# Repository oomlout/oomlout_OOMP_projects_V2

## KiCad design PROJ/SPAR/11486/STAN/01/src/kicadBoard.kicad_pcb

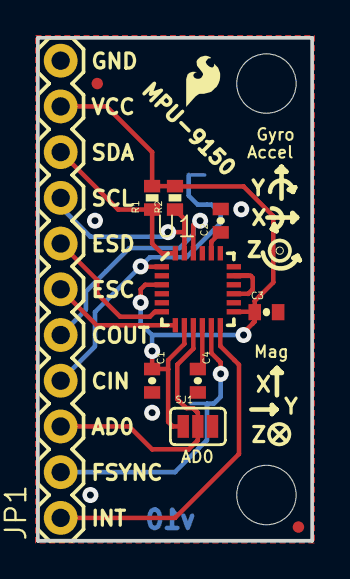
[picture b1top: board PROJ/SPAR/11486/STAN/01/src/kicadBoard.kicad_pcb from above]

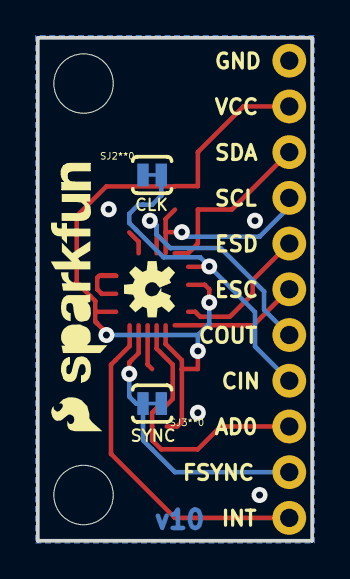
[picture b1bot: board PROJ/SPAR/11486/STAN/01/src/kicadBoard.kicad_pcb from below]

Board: 2 copper layers, 15.2 x 27.9 mm, 19 parts (5 on the bottom side), 13 nets.

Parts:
C1, C4: 0.1uF; 0402-CAP
C2: 2.2nF; 0402-CAP
C3: 10nF; 0402-CAP
JP1: M11PTH; 1X11
JP2, JP3: STAND-OFF
JP4: LOGO-SFENW2; SFE-NEW-WEB
JP5, JP6: LOGO-SFESK; SFE-LOGO-FLAME
JP7, JP8: FIDUCIALUFIDUCIAL; MICRO-FIDUCIAL
R1, R2: 10k; 0402-RES
SJ1: SJ_3_PASTE2&3
SJ2**0, SJ3**0: SOLDERJUMPERTRACE; SJ_2S-TRACE
U1: MPU-9150; QFN-24-NP
U$1: OSHW-LOGOS; OSHW-LOGO-S

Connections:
AD0: JP1.3, SJ1.2, U1.9
CLKIN: JP1.4, SJ2**0.2, U1.1
CLKOUT: JP1.5, U1.22
ESC: JP1.6, U1.7
ESD: JP1.7, U1.6
FSYNC: JP1.2, SJ3**0.2, U1.11
GND: C1.2, C2.2, C3.2, C4.2, JP1.11, SJ1.3, SJ2**0.1, SJ3**0.1, U1.15, U1.17, U1.18
INT: JP1.1, U1.12
unnamed: C2.1, U1.20
unnamed: C4.1, U1.10
SCL: JP1.8, R2.1, U1.23
SDA: JP1.9, R1.1, U1.24
VCC: C1.1, C3.1, JP1.10, R1.2, R2.2, SJ1.1, U1.3, U1.8, U1.13

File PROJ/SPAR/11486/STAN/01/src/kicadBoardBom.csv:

"Id";"Designator";"Package";"Quantity";"Designation";"Supplier and ref";
1;"JP5,JP6";"SFE-LOGO-FLAME";2;"LOGO-SFESK";;;
2;"U1";"QFN-24-NP";1;"MPU-9150";;;
3;"C1,C4";"0402-CAP";2;"0.1uF";;;
4;"JP8,JP7";"MICRO-FIDUCIAL";2;"FIDUCIALUFIDUCIAL";;;
5;"R2,R1";"0402-RES";2;"10k";;;
6;"SJ1";"SJ_3_PASTE2&3";1;"";;;
7;"C2";"0402-CAP";1;"2.2nF";;;
8;"JP1";"1X11";1;"M11PTH";;;
9;"JP2,JP3";"STAND-OFF";2;"STAND-OFF";;;
10;"C3";"0402-CAP";1;"10nF";;;
11;"SJ2**0,SJ3**0";"SJ_2S-TRACE";2;"SOLDERJUMPERTRACE";;;
12;"U$1";"OSHW-LOGO-S";1;"OSHW-LOGOS";;;
13;"JP4";"SFE-NEW-WEB";1;"LOGO-SFENW2";;;

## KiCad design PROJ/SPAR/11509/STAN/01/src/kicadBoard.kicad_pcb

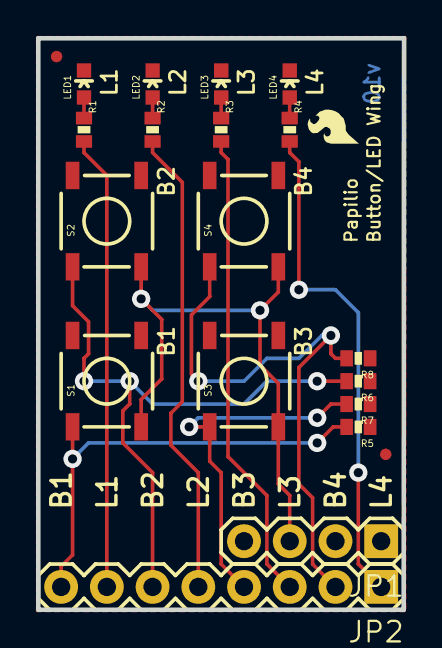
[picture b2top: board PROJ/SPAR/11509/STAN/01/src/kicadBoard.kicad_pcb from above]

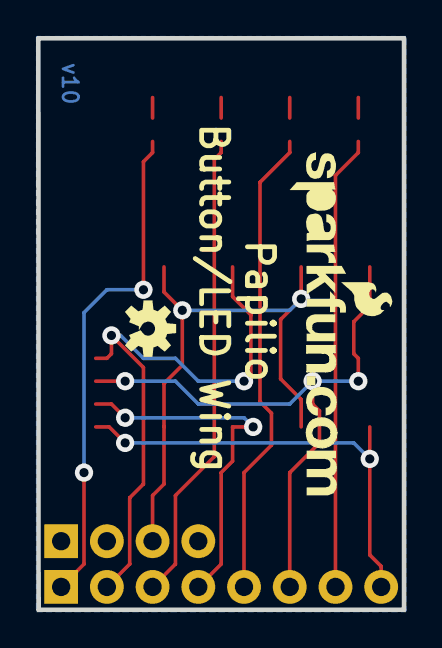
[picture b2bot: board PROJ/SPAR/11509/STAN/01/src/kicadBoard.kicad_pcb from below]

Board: 2 copper layers, 20.3 x 31.8 mm, 24 parts (2 on the bottom side), 14 nets.

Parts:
FRAME1: FRAME-LETTER; CREATIVE_COMMONS
JP1: 1X04
JP2: 1X08
JP3: LOGO-SFESK; SFE-LOGO-FLAME
JP4: LOGO-SFENEW; SFE-NEW-WEBLOGO
JP5, JP6: FIDUCIALUFIDUCIAL; MICRO-FIDUCIAL
LED1: Red; LED-0603
LED2: Yellow; LED-0603
LED3: Green; LED-0603
LED4: Blue; LED-0603
R1, R2, R3, R4: 220; 0402-RES
R5, R6, R7, R8: 10k; 0402-RES
S1: Button 1; TACTILE_SWITCH_SMD
S2: Button 2; TACTILE_SWITCH_SMD
S3: Button 3; TACTILE_SWITCH_SMD
S4: Button 4; TACTILE_SWITCH_SMD
U$1: OSHW-LOGOS; OSHW-LOGO-S

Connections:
3.3V: JP1.3, S1.3, S2.3, S3.3, S4.3
GND: JP1.1, LED1.C, LED2.C, LED3.C, LED4.C, R5.1, R6.1, R7.1, R8.1
LED1: JP2.7, R1.2
LED2: JP2.5, R2.2
LED3: JP2.3, R3.2
LED4: JP2.1, R4.2
unnamed: LED1.A, R1.1
unnamed: LED3.A, R3.1
unnamed: LED2.A, R2.1
unnamed: LED4.A, R4.1
PB1: JP2.8, R5.2, S1.1
PB2: JP2.6, R6.2, S2.1
PB3: JP2.4, R7.2, S3.1
PB4: JP2.2, R8.2, S4.1

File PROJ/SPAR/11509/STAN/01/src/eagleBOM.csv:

"Part";"Value";"Device";"Package";"Description";"";
"FRAME1";"FRAME-LETTER";"FRAME-LETTER";"CREATIVE_COMMONS";"Schematic Frame";"";
"JP1";"";"M04PTH";"1X04";"Header 4";"";
"JP2";"";"M081X08";"1X08";"Header 8";"";
"JP3";"LOGO-SFESK";"LOGO-SFESK";"SFE-LOGO-FLAME";"Spark Fun Electronics PCB Logo";"";
"JP4";"LOGO-SFENEW";"LOGO-SFENEW";"SFE-NEW-WEBLOGO";"Spark Fun Electronics PCB Logo";"";
"JP5";"FIDUCIALUFIDUCIAL";"FIDUCIALUFIDUCIAL";"MICRO-FIDUCIAL";"Fiducial Alignment Points";"";
"JP6";"FIDUCIALUFIDUCIAL";"FIDUCIALUFIDUCIAL";"MICRO-FIDUCIAL";"Fiducial Alignment Points";"";
"LED1";"Red";"LED0603";"LED-0603";"LEDs";"";
"LED2";"Yellow";"LED0603";"LED-0603";"LEDs";"";
"LED3";"Green";"LED0603";"LED-0603";"LEDs";"";
"LED4";"Blue";"LED0603";"LED-0603";"LEDs";"";
"R1";"220";"RESISTOR0402-RES";"0402-RES";"Resistor";"";
"R2";"220";"RESISTOR0402-RES";"0402-RES";"Resistor";"";
"R3";"220";"RESISTOR0402-RES";"0402-RES";"Resistor";"";
"R4";"220";"RESISTOR0402-RES";"0402-RES";"Resistor";"";
"R5";"10k";"RESISTOR0402-RES";"0402-RES";"Resistor";"";
"R6";"10k";"RESISTOR0402-RES";"0402-RES";"Resistor";"";
"R7";"10k";"RESISTOR0402-RES";"0402-RES";"Resistor";"";
"R8";"10k";"RESISTOR0402-RES";"0402-RES";"Resistor";"";
"S1";"Button 1";"SWITCH-MOMENTARY-2SMD";"TACTILE_SWITCH_SMD";"Various NO switches- pushbuttons, reed, etc";"";
"S2";"Button 2";"SWITCH-MOMENTARY-2SMD";"TACTILE_SWITCH_SMD";"Various NO switches- pushbuttons, reed, etc";"";
"S3";"Button 3";"SWITCH-MOMENTARY-2SMD";"TACTILE_SWITCH_SMD";"Various NO switches- pushbuttons, reed, etc";"";
"S4";"Button 4";"SWITCH-MOMENTARY-2SMD";"TACTILE_SWITCH_SMD";"Various NO switches- pushbuttons, reed, etc";"";
"U$1";"OSHW-LOGOS";"OSHW-LOGOS";"OSHW-LOGO-S";"Open Source Hardware Logo This logo indicates the piece of hardware it is found on incorporates a OSHW license and/or adheres to the definition of open source hardware found here: http://freedomdefined.org/OSHW";"";

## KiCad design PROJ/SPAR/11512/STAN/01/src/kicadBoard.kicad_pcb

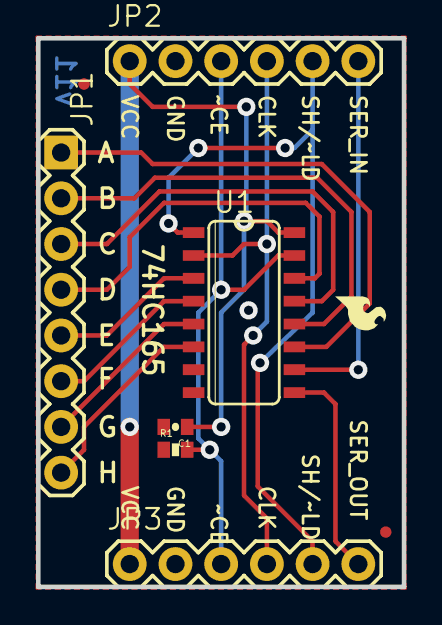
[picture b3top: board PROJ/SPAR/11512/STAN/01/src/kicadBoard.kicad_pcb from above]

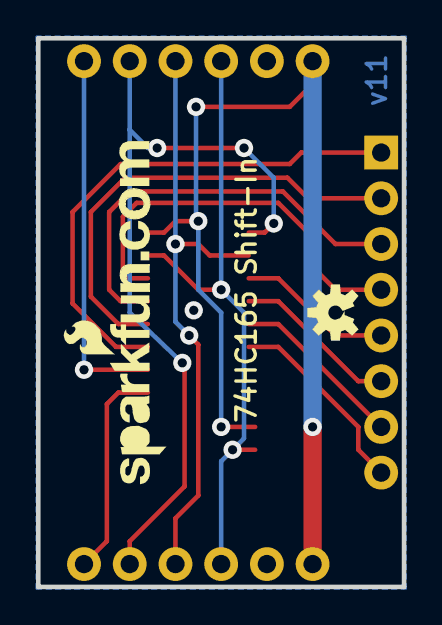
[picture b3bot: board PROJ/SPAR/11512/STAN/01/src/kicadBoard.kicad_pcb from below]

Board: 2 copper layers, 20.3 x 30.5 mm, 12 parts (2 on the bottom side), 15 nets.

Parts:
C1: .1uF; 0402-CAP
FRAME1: FRAME-LETTER; CREATIVE_COMMONS
JP1: 1X08
JP2, JP3: 1X06
JP4: LOGO-SFESK; SFE-LOGO-FLAME
JP5: LOGO-SFENEW; SFE-NEW-WEBLOGO
JP6, JP7: FIDUCIALUFIDUCIAL; MICRO-FIDUCIAL
R1: 10k; 0402-RES
U1: 74HC165D; SO16
U$1: OSHW-LOGOS; OSHW-LOGO-S

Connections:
A: JP1.1, U1.11
B: JP1.2, U1.12
C: JP1.3, U1.13
CLK: JP2.4, JP3.4, U1.2
D: JP1.4, U1.14
E: JP1.5, U1.3
F: JP1.6, U1.4
G: JP1.7, U1.5
GND: C1.2, JP2.2, JP3.2, R1.1, U1.8
H: JP1.8, U1.6
SERIAL_IN: JP2.6, U1.10
SERIAL_OUT: JP3.6, U1.9
SHIFT/~LOAD: JP2.5, JP3.5, U1.1
VCC: C1.1, JP2.1, JP3.1, U1.16
~CLK_ENABLE: JP2.3, JP3.3, R1.2, U1.15

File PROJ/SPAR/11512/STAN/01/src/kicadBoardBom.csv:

"Id";"Designator";"Package";"Quantity";"Designation";"Supplier and ref";
1;"R1";"0402-RES";1;"10k";;;
2;"JP2,JP3";"1X06";2;"";;;
3;"FRAME1";"CREATIVE_COMMONS";1;"FRAME-LETTER";;;
4;"JP7,JP6";"MICRO-FIDUCIAL";2;"FIDUCIALUFIDUCIAL";;;
5;"C1";"0402-CAP";1;".1uF";;;
6;"JP1";"1X08";1;"";;;
7;"JP4";"SFE-LOGO-FLAME";1;"LOGO-SFESK";;;
8;"U1";"SO16";1;"74HC165D";;;
9;"JP5";"SFE-NEW-WEBLOGO";1;"LOGO-SFENEW";;;
10;"U$1";"OSHW-LOGO-S";1;"OSHW-LOGOS";;;

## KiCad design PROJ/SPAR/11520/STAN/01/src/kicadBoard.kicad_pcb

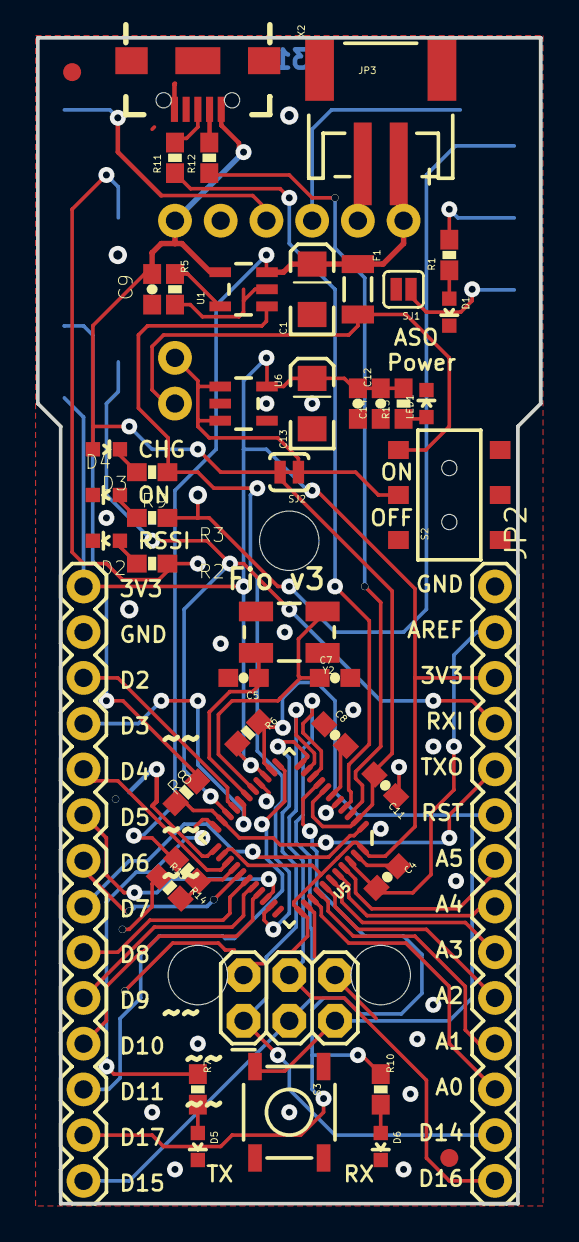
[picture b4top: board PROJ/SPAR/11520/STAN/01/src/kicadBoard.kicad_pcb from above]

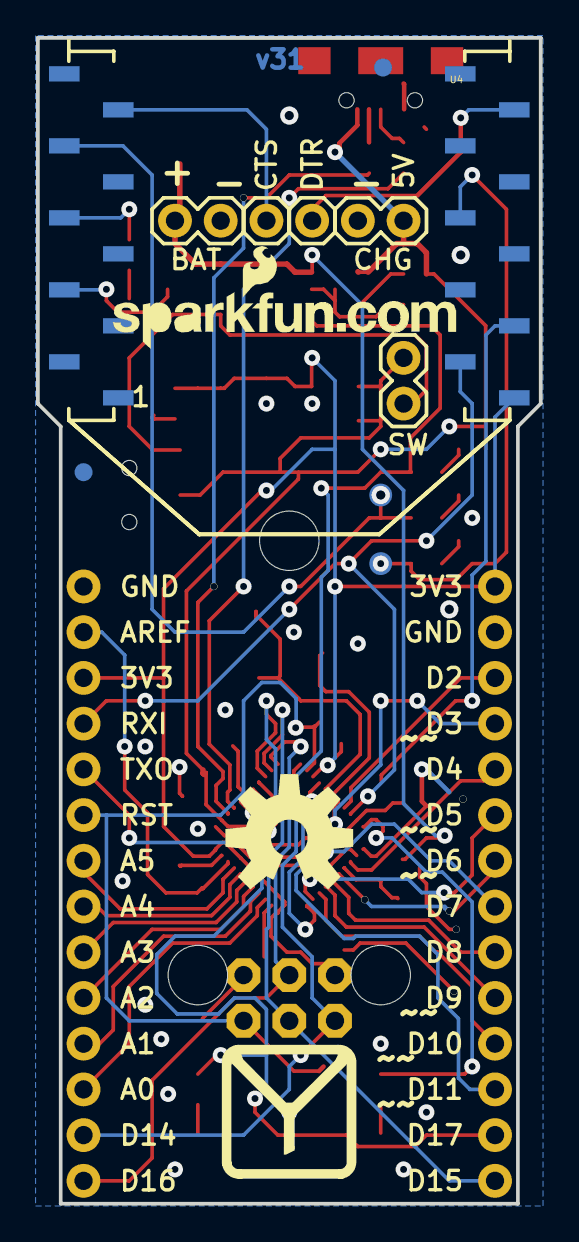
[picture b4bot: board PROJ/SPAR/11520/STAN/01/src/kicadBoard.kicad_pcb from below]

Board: 2 copper layers, 27.9 x 64.8 mm, 66 parts (12 on the bottom side), 55 nets.

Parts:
C1, C13: 10uF; EIA3216
C4, C14: 0.1uF; 0603-CAP
C5, C7: 22pF; 0603-CAP
C8, C11, C12: 1uF; 0603-CAP
C9: 4.7uF; 0603-CAP
D1, D4, D5: Yellow; LED-0603
D2: Green; LED-0603
D3: Red; LED-0603
D6: Blue; LED-0603
F1: PTCSMD; PTC-1206
FRAME1, FRAME2: FRAME-LETTER; CREATIVE_COMMONS
JP1, JP2: M14; 1X14
JP3: JST-2-SMD
JP4: AVR_SPI; 2X3
JP5, JP16, JP17: STAND-OFF
JP6: External Charge; 1X02
JP7: External Switch; 1X02
JP8, JP9: 1X01
JP10, JP11, JP12, JP13: FIDUCIALUFIDUCIAL; FIDUCIAL-1X2
JP14: External Power; 1X02
LED1: Red; LED-0603
LOGO1: OSHW-LOGOL; OSHW-LOGO-L
R1, R2, R3, R7, R10, R13: 330; 0603-RES
R5: 2K; 0603-RES
R6: 10K; 0603-RES
R8: 100; 0603-RES
R9: 470; 0603-RES
R11, R12: 22; 0603-RES
R14, R15: 1k; 0603-RES
S2: Power Switch; AYZ0202
S3: Reset; TACTILE_SWITCH_SMD
SJ1: SOLDERJUMPERNC; SJ_2S
SJ2: USB Power; SJ_2S-TRACE
TP1: RSSI; PAD.03X.05
TP2: ON; PAD.03X.05
U1: MCP73831; SOT23-5
U4: XBEE; XBEE-SMD
U5: ATmega32U4; QFN-44-NOPAD_1_1
U6: MIC5219-3.3; SOT23-5
U$1: LOGO-SFENEW; SFE-NEW-WEBLOGO
U$2: REVISION
U$6: FIO_LOGOV2; FUNNEL_LOGO_BOTTOM_V2
X2: USB_MICROB_PLUGCONN-11752; USB-B-MICRO-SMD_V03
Y2: 8MHz; CRYSTAL-SMD-5X3

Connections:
3.3V: C12.1, C13.A, C14.2, JP1.1, JP2.3, JP4.2, R6.2, R13.2, U4.1, U5.14, U5.24, U5.34, U5.44, U6.5
A0: JP2.12, U5.36
A1: JP2.11, U5.37
A2: JP2.10, U5.38
A3: JP2.9, U5.39
A4: JP2.8, U5.40
A5: JP2.7, U5.41
AREF: C4.2, JP2.2, U5.42
ASSOCIATE: R1.2, U4.15
CHARGE_STAT: R9.1, U1.1, U5.32
CTS: JP8.1, U4.12
D2: JP1.3, U5.19
D3: JP1.4, U5.18
D4: JP1.5, U5.25
D5: JP1.6, U5.31
D6: JP1.7, U5.27
D7: JP1.8, U5.1
D8: JP1.9, U5.28
D9: JP1.10, U5.29
D10: JP1.11, U5.30
D11: JP1.12, U5.12
D17: JP1.13, R10.1, U5.8
D+: R11.1, U5.4
D-: R12.1, U5.3
GND: C1.C, C4.1, C5.2, C7.2, C8.1, C9.2, C11.1, C12.2, C13.C, C14.1, D1.C, D2.C, D3.C, D5.C, D6.C, JP1.2, JP2.1, JP3.1, JP4.6, JP6.1, JP14.1, LED1.C, R5.2, R15.1, S3.1, U1.2, U4.10, U5.5, U5.15, U5.23, U5.33, U5.35, U5.43, U6.2, X2.GND1
MISO: JP2.13, JP4.1, U5.11
MOSI: JP2.14, JP4.4, U5.10
unnamed: R3.2, TP2.P$1, U4.13
unnamed: D1.A, R1.1
unnamed: D2.A, R2.1
unnamed: R2.2, TP1.P$1, U4.6
unnamed: R11.2, X2.D+1
unnamed: D3.A, R3.1
unnamed: R8.2, U4.3
unnamed: D4.C, R9.2
unnamed: F1.2, JP7.2, S2.3
unnamed: R5.1, U1.5
unnamed: SJ1.1, U4.17
unnamed: D5.A, R7.2
unnamed: C7.1, U5.16, Y2.1
unnamed: C5.1, U5.17, Y2.3
unnamed: D6.A, R10.2
unnamed: R12.2, X2.D-1
unnamed: LED1.A, R13.1
RAW: JP7.1, S2.2, SJ2.1, U6.1, U6.3
RST: JP2.6, JP4.5, R6.1, S3.3, U5.13
RXI: JP2.4, U4.2, U5.20
SCK: JP1.14, JP4.3, U5.9
SLEEP_RQ: JP9.1, U4.9
TXLED: R7.1, U5.22
TXO: JP2.5, R8.1, U5.21
UCAP: C8.2, U5.6
USB_VCC: C9.1, C11.2, D4.A, JP6.2, SJ2.2, U1.4, U5.2, U5.7, X2.VBUS
VBATT: C1.A, F1.1, JP3.2, JP14.2, R14.2, U1.3
VBATT_LVL: R14.1, R15.2, U5.26

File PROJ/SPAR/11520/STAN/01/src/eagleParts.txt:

Partlist

Exported from boardEagle.brd at 17/08/2022 21:16

EAGLE Version 9.6.2 Copyright (c) 1988-2020 Autodesk, Inc.

Assembly variant: 

Part     Value                     Package             Library                     Position (inch)       Orientation

C1       10uF                      EIA3216             SparkFun                    (0.55 2)              R90
C4       0.1uF                     0603-CAP            SparkFun-Capacitors         (0.71437008 0.71437008) R225
C5       22pF                      0603-CAP            SparkFun-Capacitors         (0.4 1.15)            R180
C7       22pF                      0603-CAP            SparkFun-Capacitors         (0.6 1.15)            R0
C8       1uF                       0603-CAP            SparkFun-Capacitors         (0.6 1.025)           R315
C9       4.7uF                     0603-CAP            SparkFun-Capacitors         (0.2 2)               R270
C11      1uF                       0603-CAP            SparkFun-Capacitors         (0.71 0.915)          R135
C12      1uF                       0603-CAP            SparkFun-Capacitors         (0.65 1.75)           R270
C13      10uF                      EIA3216             SparkFun                    (0.55 1.75)           R90
C14      0.1uF                     0603-CAP            SparkFun-Capacitors         (0.7 1.75)            R90
D1       Yellow                    LED-0603            SparkFun                    (0.85 1.95)           R180
D2       Green                     LED-0603            SparkFun                    (0.1 1.45)            R90
D3       Red                       LED-0603            SparkFun                    (0.1 1.55)            R90
D4       Yellow                    LED-0603            SparkFun                    (0.1 1.65)            R270
D5       Yellow                    LED-0603            SparkFun                    (0.3 0.125)           R180
D6       Blue                      LED-0603            SparkFun                    (0.7 0.125)           R180
F1       PTCSMD                    PTC-1206            SparkFun                    (0.65 2)              R270
JP1      M14                       1X14                SparkFun                    (0.05 1.35)           R270
JP2      M14                       1X14                SparkFun                    (0.95 1.35)           R270
JP3                                JST-2-SMD           SparkFun                    (0.7 2.42)            R0
JP4      AVR_SPI                   2X3                 SparkFun                    (0.4 0.4)             R0
JP6      External Charge           1X02                SparkFun                    (0.35 2.15)           MR0
JP7      External Switch           1X02                SparkFun                    (0.25 1.85)           MR270
JP8                                1X01                SparkFun                    (0.55 2.15)           MR0
JP9                                1X01                SparkFun                    (0.45 2.15)           MR0
JP10     FIDUCIALUFIDUCIAL         FIDUCIAL-1X2        SparkFun                    (0.85 0.1)            R0
JP11     FIDUCIALUFIDUCIAL         FIDUCIAL-1X2        SparkFun                    (0.025 2.475)         R0
JP12     FIDUCIALUFIDUCIAL         FIDUCIAL-1X2        SparkFun                    (0.295 2.485)         MR0
JP13     FIDUCIALUFIDUCIAL         FIDUCIAL-1X2        SparkFun                    (0.95 1.6)            MR0
JP14     External Power            1X02                SparkFun                    (0.65 2.15)           MR180
LED1     Red                       LED-0603            SparkFun                    (0.8 1.75)            R0
R1       330                       0603-RES            SparkFun-Resistors          (0.85 2.075)          R90
R2       330                       0603-RES            SparkFun-Resistors          (0.2 1.4)             R0
R3       330                       0603-RES            SparkFun-Resistors          (0.2 1.5)             R0
R5       2K                        0603-RES            SparkFun-Resistors          (0.25 2)              R270
R6       10K                       0603-RES            SparkFun-Resistors          (0.41 1.03)           R225
R7       330                       0603-RES            SparkFun-Resistors          (0.3 0.25)            R270
R8       100                       0603-RES            SparkFun-Resistors          (0.275 0.9)           R45
R9       470                       0603-RES            SparkFun-Resistors          (0.2 1.6)             R180
R10      330                       0603-RES            SparkFun-Resistors          (0.7 0.25)            R270
R11      22                        0603-RES            SparkFun-Resistors          (0.25 2.2875)         R90
R12      22                        0603-RES            SparkFun-Resistors          (0.325 2.2875)        R90
R13      330                       0603-RES            SparkFun-Resistors          (0.75 1.75)           R90
R14      1k                        0603-RES            SparkFun-Resistors          (0.2761811 0.72956693) R135
R15      1k                        0603-RES            SparkFun-Resistors          (0.23858268 0.69098425) R315
S2       Power Switch              AYZ0202             SparkFun                    (0.85 1.55)           R90
S3       Reset                     TACTILE_SWITCH_SMD  SparkFun                    (0.5 0.2)             R270
SJ1      SOLDERJUMPERNC            SJ_2S               SparkFun                    (0.75 2)              R180
SJ2      USB Power                 SJ_2S-TRACE         SparkFun                    (0.5 1.6)             R180
TP1      RSSI                      PAD.03X.05          SparkFun                    (0.3 1.4)             MR0
TP2      ON                        PAD.03X.05          SparkFun                    (0.3 1.55)            MR0
U1       MCP73831                  SOT23-5             SparkFun                    (0.4 2)               R90
U4       XBEE                      XBEE-SMD            SparkFun                    (0.5 2.55)            MR180
U5       ATmega32U4                QFN-44-NOPAD_1:1    SparkFun-IC-Microcontroller (0.5 0.8)             R225
U6       MIC5219-3.3               SOT23-5             SparkFun                    (0.4 1.75)            R270
X2       USB_MICROB_PLUGCONN-11752 USB-B-MICRO-SMD_V03 SparkFun-Connectors         (0.3 2.5)             R270
Y2       8MHz                      CRYSTAL-SMD-5X3     SparkFun                    (0.5 1.25)            R180

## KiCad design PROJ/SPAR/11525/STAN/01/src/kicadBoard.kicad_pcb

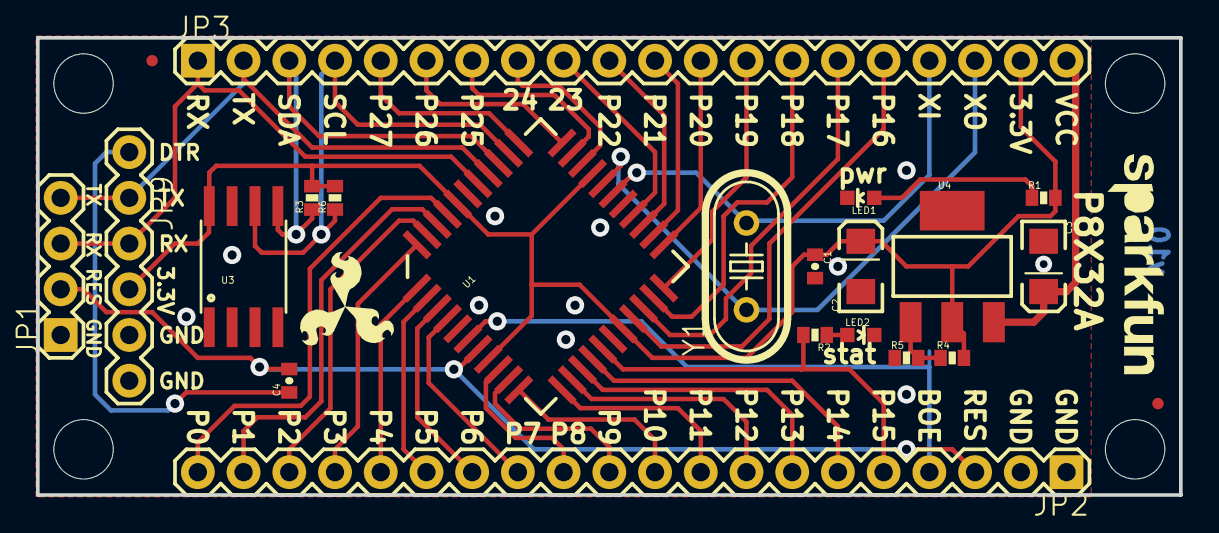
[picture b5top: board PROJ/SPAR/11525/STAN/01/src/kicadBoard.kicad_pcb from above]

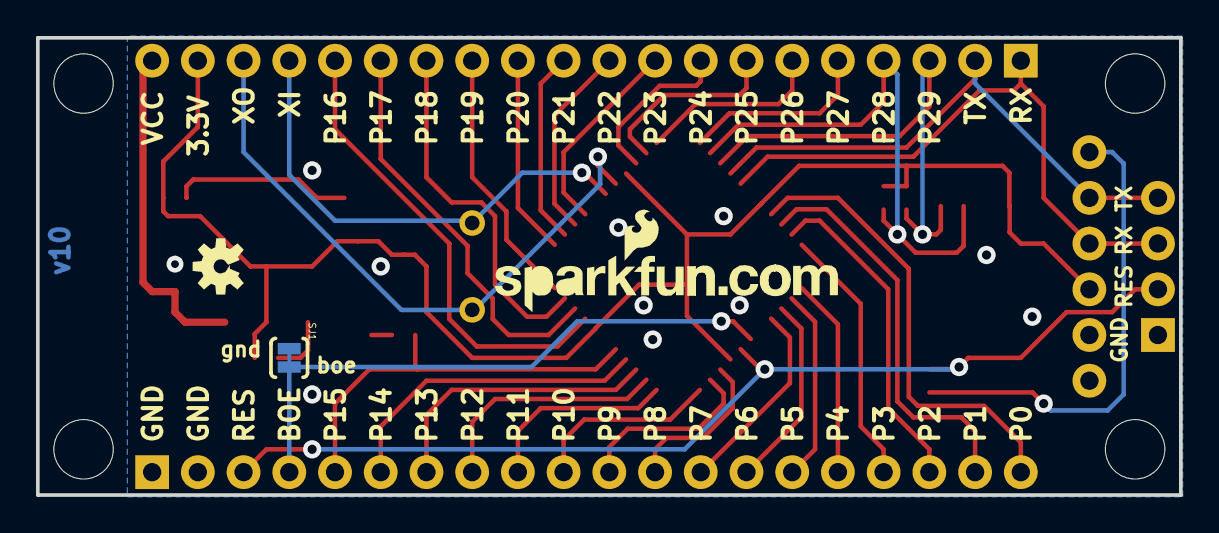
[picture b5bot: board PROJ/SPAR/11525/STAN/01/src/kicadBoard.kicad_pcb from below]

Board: 2 copper layers, 63.5 x 25.4 mm, 34 parts (3 on the bottom side), 43 nets.

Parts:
C1, C4: 0.1uF; 0402-CAP
C2, C3: 10uF; EIA3216
FRAME1: FRAME-LETTER; CREATIVE_COMMONS
JP1: PropPlug; 1X04
JP2, JP3: M20; 1X20
JP4, JP15: FIDUCIALUFIDUCIAL; MICRO-FIDUCIAL
JP5: LOGO-SFENEW; SFE-NEW-WEBLOGO
JP6, JP7, JP8: LOGO-SFESK; SFE-LOGO-FLAME
JP9: FTDI_BASICPTH; FTDI_BASIC
JP10, JP11, JP12, JP13: STAND-OFF
JP14: LOGO-SFENW2; SFE-NEW-WEB
LED1: red; LED-0603
LED2: yellow; LED-0603
R1, R2: 330; 0402-RES
R3, R6: 10k; 0402-RES
R4: 240; 0402-RES
R5: 390; 0402-RES
SJ1: SOLDERJUMPERTRACE; SJ_2S-TRACE
U1: P8X32A-Q44
U3: EEPROM-I2CEIAJ; SO08-EIAJ
U4: V_REG_317SMD; SOT223
U$1: OSHW-LOGOS; OSHW-LOGO-S
Y1: HC49U-V

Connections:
3.3V: C1.1, C2.A, JP3.19, JP9.VCC, R1.2, R3.2, R4.2, R6.2, U1.8, U1.18, U1.30, U1.40, U3.8, U4.2
BOE: JP2.4, SJ1.2, U1.6
GND: C1.2, C2.C, C3.C, JP1.1, JP2.1, JP2.2, JP9.CTS, JP9.GND, LED1.C, LED2.C, R5.1, SJ1.1, U1.5, U1.17, U1.27, U1.39, U3.1, U3.2, U3.3, U3.4, U3.7
unnamed: LED1.A, R1.1
unnamed: LED2.A, R2.1
unnamed: R4.1, R5.2, U4.1
unnamed: C4.1, JP9.DTR
P0: JP2.20, U1.41
P1: JP2.19, U1.42
P2: JP2.18, U1.43
P3: JP2.17, U1.44
P4: JP2.16, U1.1
P5: JP2.15, U1.2
P6: JP2.14, U1.3
P7: JP2.13, U1.4
P8: JP2.12, U1.9
P9: JP2.11, U1.10
P10: JP2.10, U1.11
P11: JP2.9, U1.12
P12: JP2.8, U1.13
P13: JP2.7, U1.14
P14: JP2.6, U1.15
P15: JP2.5, R2.2, U1.16
P16: JP3.16, U1.19
P17: JP3.15, U1.20
P18: JP3.14, U1.21
P19: JP3.13, U1.22
P20: JP3.12, U1.23
P21: JP3.11, U1.24
P22: JP3.10, U1.25
P23: JP3.9, U1.26
P24: JP3.8, U1.31
P25: JP3.7, U1.32
P26: JP3.6, U1.33
P27: JP3.5, U1.34
RES: C4.2, JP1.2, JP2.3, U1.7
RX: JP1.3, JP3.1, JP9.TXO, U1.38
SCL: JP3.4, R6.1, U1.35, U3.6
SDA: JP3.3, R3.1, U1.36, U3.5
TX: JP1.4, JP3.2, JP9.RXI, U1.37
VCC: C3.A, JP3.20, U4.3
XI: JP3.17, U1.28, Y1.2
XO: JP3.18, U1.29, Y1.1

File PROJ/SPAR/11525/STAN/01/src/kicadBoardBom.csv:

"Id";"Designator";"Package";"Quantity";"Designation";"Supplier and ref";
1;"JP4,JP15";"MICRO-FIDUCIAL";2;"FIDUCIALUFIDUCIAL";;;
2;"JP13,JP12,JP11,JP10";"STAND-OFF";4;"STAND-OFF";;;
3;"R4";"0402-RES";1;"240";;;
4;"FRAME1";"CREATIVE_COMMONS";1;"FRAME-LETTER";;;
5;"C4,C1";"0402-CAP";2;"0.1uF";;;
6;"LED2";"LED-0603";1;"yellow";;;
7;"R1,R2";"0402-RES";2;"330";;;
8;"JP8,JP7,JP6";"SFE-LOGO-FLAME";3;"LOGO-SFESK";;;
9;"JP1";"1X04";1;"PropPlug";;;
10;"Y1";"HC49U-V";1;"";;;
11;"U1";"P8X32A-Q44";1;"";;;
12;"JP2,JP3";"1X20";2;"M20";;;
13;"R5";"0402-RES";1;"390";;;
14;"R3,R6";"0402-RES";2;"10k";;;
15;"JP9";"FTDI_BASIC";1;"FTDI_BASICPTH";;;
16;"U3";"SO08-EIAJ";1;"EEPROM-I2CEIAJ";;;
17;"C2,C3";"EIA3216";2;"10uF";;;
18;"LED1";"LED-0603";1;"red";;;
19;"JP14";"SFE-NEW-WEB";1;"LOGO-SFENW2";;;
20;"U4";"SOT223";1;"V_REG_317SMD";;;
21;"JP5";"SFE-NEW-WEBLOGO";1;"LOGO-SFENEW";;;
22;"U$1";"OSHW-LOGO-S";1;"OSHW-LOGOS";;;
23;"SJ1";"SJ_2S-TRACE";1;"SOLDERJUMPERTRACE";;;

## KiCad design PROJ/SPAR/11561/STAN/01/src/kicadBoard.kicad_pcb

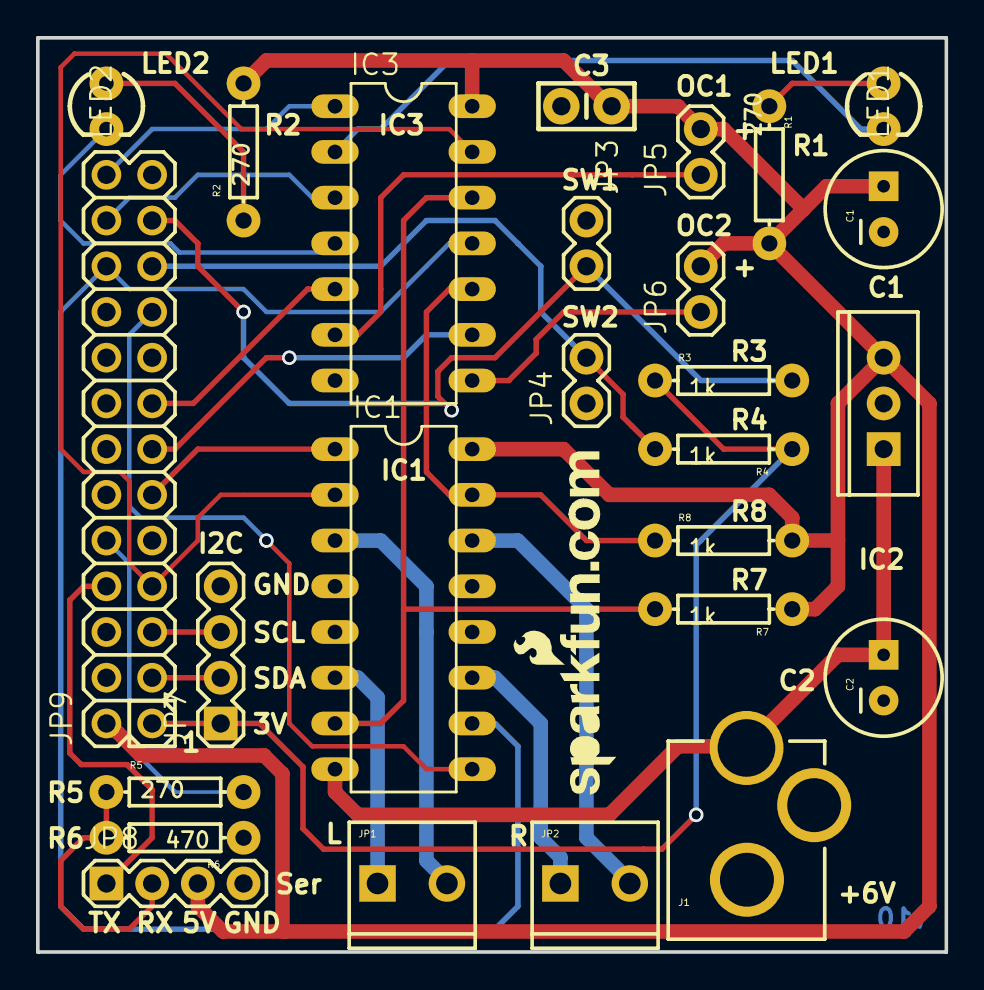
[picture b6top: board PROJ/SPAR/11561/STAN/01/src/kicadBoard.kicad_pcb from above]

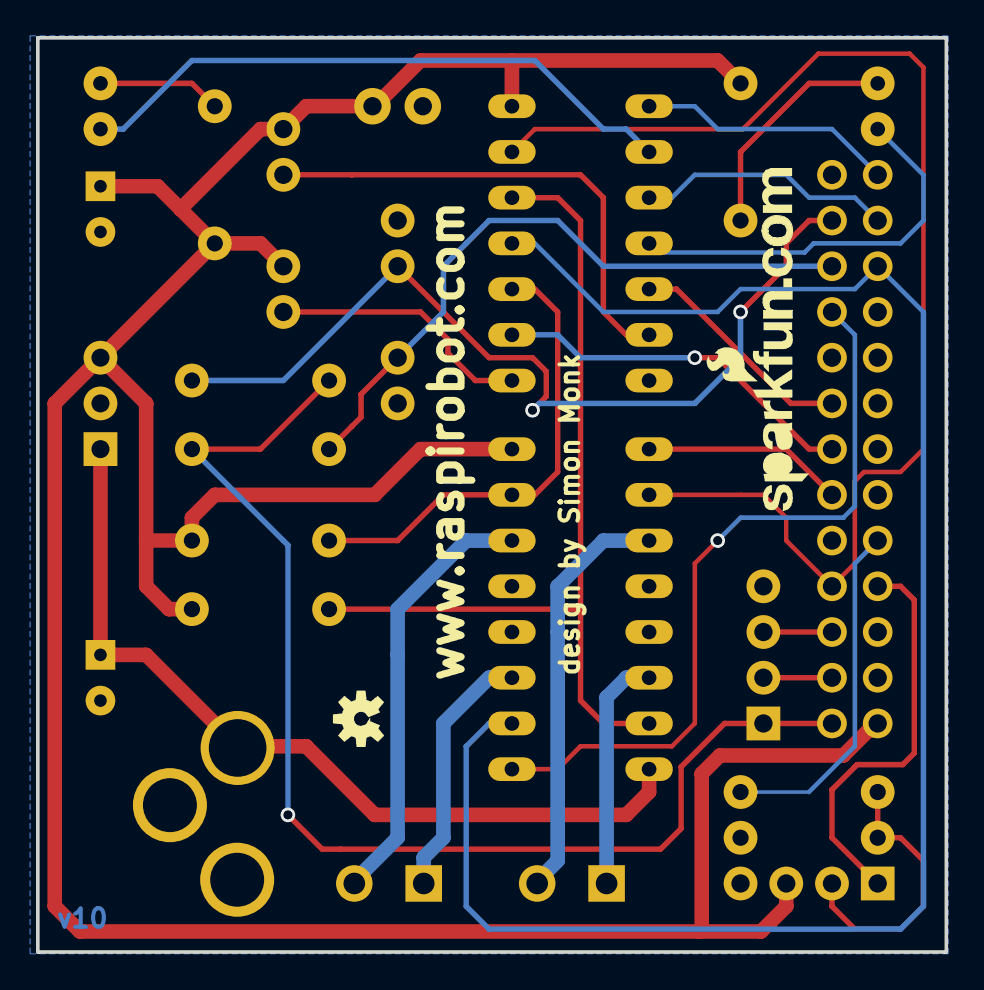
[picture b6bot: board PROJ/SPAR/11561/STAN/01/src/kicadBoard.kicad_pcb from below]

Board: 2 copper layers, 50.5 x 50.8 mm, 30 parts (2 on the bottom side), 31 nets.

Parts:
C1: 100uF; CPOL-RADIAL-100UF-25V
C2: 220uF; CPOL-RADIAL-100UF-25V
C3: 0.1uF; CAP-PTH-SMALL-KIT
FRAME1: FRAME-LETTER; CREATIVE_COMMONS
IC1: L293D; DIL16
IC2: LM2940CT-5.0; TO220-IGO
IC3: 7406N; DIL14
J1: POWER_JACKPTH_LOCK; POWER_JACK_PTH_LOCK
JP1, JP2: SCREWTERMINAL-3.5MM-2_LOCK
JP3: SW1; 1X02
JP4: SW2; 1X02
JP5, JP6: 1X02
JP7: I2C; 1X04
JP8: UART; 1X04
JP9: M13X22X13; 2X13
JP10, JP11: LOGO-SFENEW; SFE-NEW-WEBLOGO
LED1: green; LED3MM
LED2: yellow; LED3MM
R1, R2, R5: 270; AXIAL-0.3EZ
R3, R4, R7, R8: 1k; AXIAL-0.3EZ
R6: 470; AXIAL-0.3EZ
U$4: OSHW-LOGOS; OSHW-LOGO-S

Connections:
1-2EN: IC1.1, JP9.11
1A: IC1.2, IC3.13, JP9.7
3-4EN: IC1.9, JP9.19
3.3V: JP7.1, JP9.1, R3.P$1, R4.P$1
3A: IC1.10, IC3.11, JP9.22
C: IC3.5, JP9.15
D: IC3.9, JP9.13
GND: C1.2, C2.2, C3.2, IC1.4, IC1.5, IC1.12, IC1.13, IC2.GND, IC3.7, J1.GND, J1.GNDBREAK, JP3.1, JP4.1, JP7.4, JP8.4, JP9.6, R6.P$1
LED1: IC3.1, JP9.26
LED2: IC3.3, JP9.24
ML1: IC1.6, JP1.1
ML2: IC1.3, JP1.2
MR1: IC1.11, JP2.1
MR2: IC1.14, JP2.2
unnamed: IC1.7, IC3.12, R7.P$2
unnamed: IC1.15, IC3.10, R8.P$1
unnamed: LED1.A, R1.P$1
unnamed: LED2.A, R2.P$1
unnamed: IC3.2, LED1.K
unnamed: IC3.4, LED2.K
unnamed: IC3.6, JP5.1
unnamed: IC3.8, JP6.1
unnamed: JP8.2, R5.P$1, R6.P$2
RX: JP9.10, R5.P$2
SCL: JP7.3, JP9.5
SDA: JP7.2, JP9.3
SW1: JP3.2, JP9.23, R3.P$2
SW2: JP4.2, JP9.21, R4.P$2
TX: JP8.1, JP9.8
VCC: C1.1, C3.1, IC1.16, IC2.OUT, IC3.14, JP5.2, JP6.2, JP8.3, JP9.2, R1.P$2, R2.P$2, R7.P$1, R8.P$2
VIN: C2.1, IC1.8, IC2.IN, J1.PWR

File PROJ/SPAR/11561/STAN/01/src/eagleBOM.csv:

"Part";"Value";"Device";"Package";"Description";"MF";"MPN";"OC_FARNELL";"OC_NEWARK";
"C1";"100uF";"CAP_POLPTH1";"CPOL-RADIAL-100UF-25V";"Capacitor Polarized";"";"";"";"";
"C2";"220uF";"CAP_POLPTH1";"CPOL-RADIAL-100UF-25V";"Capacitor Polarized";"";"";"";"";
"C3";"0.1uF";"CAPKIT";"CAP-PTH-SMALL-KIT";"Capacitor";"";"";"";"";
"FRAME1";"FRAME-LETTER";"FRAME-LETTER";"CREATIVE_COMMONS";"Schematic Frame";"";"";"";"";
"IC1";"L293D";"L293D";"DIL16";"PUSH-PULL 4 CHANNEL DRIVER";"";"L293D";"9589619";"56P8249";
"IC2";"LM2940CT-5.0";"V_REG_78XXSINK";"TO220-IGO";"Voltage Regulator";"";"";"";"";
"IC3";"7406N";"7406N";"DIL14";"Hex INVERTER, open collector high-voltage output";"";"";"";"";
"J1";"POWER_JACKPTH_LOCK";"POWER_JACKPTH_LOCK";"POWER_JACK_PTH_LOCK";"Power Jack";"";"";"";"";
"JP1";"";"M023.5MM_LOCK";"SCREWTERMINAL-3.5MM-2_LOCK";"Header 2";"";"";"";"";
"JP2";"";"M023.5MM_LOCK";"SCREWTERMINAL-3.5MM-2_LOCK";"Header 2";"";"";"";"";
"JP3";"SW1";"M02PTH";"1X02";"Header 2";"";"";"";"";
"JP4";"SW2";"M02PTH";"1X02";"Header 2";"";"";"";"";
"JP5";"";"M02PTH";"1X02";"Header 2";"";"";"";"";
"JP6";"";"M02PTH";"1X02";"Header 2";"";"";"";"";
"JP7";"I2C";"M04PTH";"1X04";"Header 4";"";"";"";"";
"JP8";"UART";"M04PTH";"1X04";"Header 4";"";"";"";"";
"JP9";"M13X22X13";"M13X22X13";"2X13";"";"";"";"";"";
"JP10";"LOGO-SFENEW";"LOGO-SFENEW";"SFE-NEW-WEBLOGO";"Spark Fun Electronics PCB Logo";"";"";"";"";
"JP11";"LOGO-SFENEW";"LOGO-SFENEW";"SFE-NEW-WEBLOGO";"Spark Fun Electronics PCB Logo";"";"";"";"";
"LED1";"green";"LED3MM";"LED3MM";"LEDs";"";"";"";"";
"LED2";"yellow";"LED3MM";"LED3MM";"LEDs";"";"";"";"";
"R1";"270";"RESISTOREZ";"AXIAL-0.3EZ";"Resistor";"";"";"";"";
"R2";"270";"RESISTOREZ";"AXIAL-0.3EZ";"Resistor";"";"";"";"";
"R3";"1k";"RESISTOREZ";"AXIAL-0.3EZ";"Resistor";"";"";"";"";
"R4";"1k";"RESISTOREZ";"AXIAL-0.3EZ";"Resistor";"";"";"";"";
"R5";"270";"RESISTOREZ";"AXIAL-0.3EZ";"Resistor";"";"";"";"";
"R6";"470";"RESISTOREZ";"AXIAL-0.3EZ";"Resistor";"";"";"";"";
"R7";"1k";"RESISTOREZ";"AXIAL-0.3EZ";"Resistor";"";"";"";"";
"R8";"1k";"RESISTOREZ";"AXIAL-0.3EZ";"Resistor";"";"";"";"";
"U$4";"OSHW-LOGOS";"OSHW-LOGOS";"OSHW-LOGO-S";"Open Source Hardware Logo This logo indicates the piece of hardware it is found on incorporates a OSHW license and/or adheres to the definition of open source hardware found here: http://freedomdefined.org/OSHW";"";"";"";"";

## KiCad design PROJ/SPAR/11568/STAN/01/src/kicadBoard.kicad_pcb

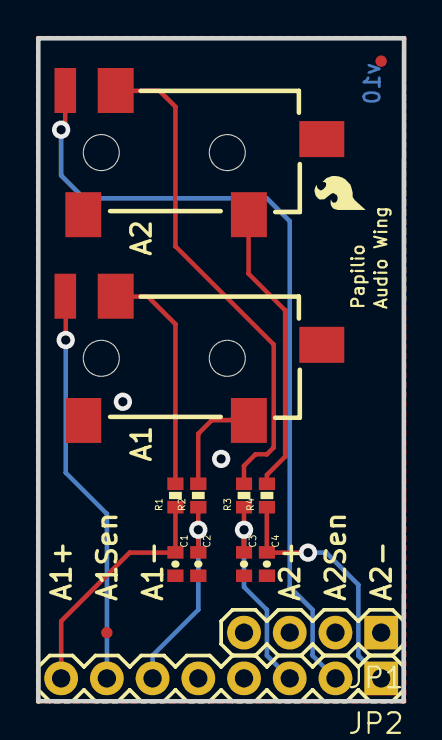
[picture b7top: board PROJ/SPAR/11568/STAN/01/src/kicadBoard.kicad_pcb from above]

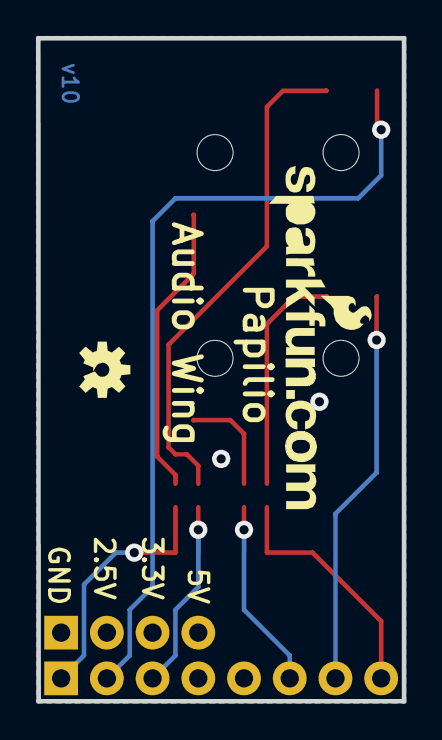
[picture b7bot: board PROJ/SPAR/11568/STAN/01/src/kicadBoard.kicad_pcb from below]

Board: 2 copper layers, 20.3 x 36.8 mm, 19 parts (2 on the bottom side), 11 nets.

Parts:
AJ1, AJ2: AUDIO-JACK2SMD; AUDIO-JACK-3.5MM-SMD
C1, C2, C3, C4: 4.7nF; 0402-CAP
FRAME1, FRAME2: FRAME-LETTER; CREATIVE_COMMONS
JP1: 1X04
JP2: 1X08
JP3: LOGO-SFESK; SFE-LOGO-FLAME
JP4: LOGO-SFENEW; SFE-NEW-WEBLOGO
JP5, JP6: FIDUCIALUFIDUCIAL; MICRO-FIDUCIAL
R1, R2, R3, R4: 3.3k; 0402-RES
U$1: OSHW-LOGOS; OSHW-LOGO-S

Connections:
A1+: C1.1, JP2.8, R1.1
A1-: C2.1, JP2.6, R2.1
A1SEN: AJ1.RSH, JP2.7
A2+: C3.1, JP2.3, R3.1
A2-: C4.1, JP2.1, R4.1
A2SEN: AJ2.RSH, JP2.2
GND: AJ1.SLEEVE, AJ2.SLEEVE, C1.2, C2.2, C3.2, C4.2, JP1.1
unnamed: AJ2.RING, R3.2
unnamed: AJ2.TIP, R4.2
unnamed: AJ1.RING, R1.2
unnamed: AJ1.TIP, R2.2

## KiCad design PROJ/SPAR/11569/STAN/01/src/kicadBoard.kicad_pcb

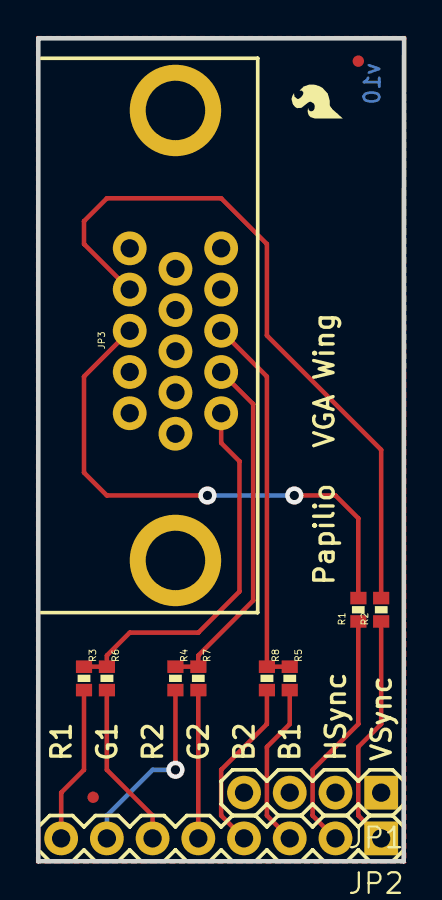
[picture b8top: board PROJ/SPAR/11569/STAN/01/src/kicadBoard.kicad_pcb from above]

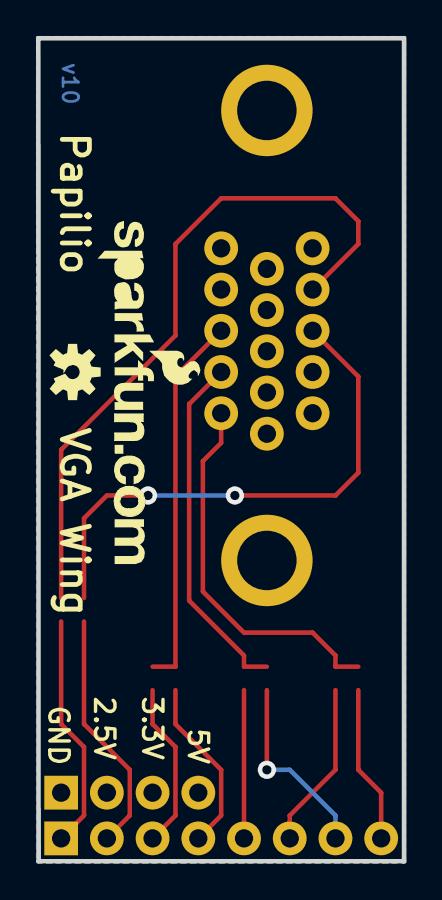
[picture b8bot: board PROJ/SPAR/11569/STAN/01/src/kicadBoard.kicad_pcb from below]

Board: 2 copper layers, 20.3 x 45.7 mm, 17 parts (2 on the bottom side), 14 nets.

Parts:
FRAME1: FRAME-LETTER; CREATIVE_COMMONS
JP1: 1X04
JP2: 1X08
JP3: DB15
JP4, JP5: FIDUCIALUFIDUCIAL; MICRO-FIDUCIAL
JP6: LOGO-SFENEW; SFE-NEW-WEBLOGO
JP7: LOGO-SFESK; SFE-LOGO-FLAME
R1, R2: 82.5; 0402-RES
R3, R4, R5, R6, R7, R8: 270; 0402-RES
U$1: OSHW-LOGOS; OSHW-LOGO-S

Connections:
BLUE: JP3.3, R5.1, R8.1
BLUE1: JP2.3, R5.2
BLUE2: JP2.4, R8.2
GND: JP1.1, JP3.6, JP3.7, JP3.8, JP3.10, JP3.11
GREEN: JP3.2, R4.1, R7.1
GREEN1: JP2.7, R4.2
GREEN2: JP2.5, R7.2
HSYNC: JP2.2, R1.1
unnamed: JP3.13, R1.2
unnamed: JP3.14, R2.2
RED: JP3.1, R3.1, R6.1
RED1: JP2.8, R3.2
RED2: JP2.6, R6.2
VSYNC: JP2.1, R2.1

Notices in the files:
parts and their libraries:
HTTP://CREATIVECOMMONS.ORG/LICENSES/BY-SA/3.0
RELEASED UNDER THE CREATIVE COMMONS ATTRIBUTION SHARE-ALIKE 3.0 LICENSE
